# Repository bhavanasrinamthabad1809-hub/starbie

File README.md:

# RECTANGLEBIE (3 button edition)

so basically starbie is a tiny digital pet that lives on your desk, kinda like a tamagotchi lol. it walks around a little oled screen, reacts when you tilt or shake it, shows the temperature and humidity, and now it also gets happy when you press its 3rd button.

# WHY I MADE THIS
to learn hardware simple . this is my first ever pcb so yeahh so excited to get my hands on it .

# WHAT IT DOES
button 1 opens the menu. when the menu is open you tilt it to move the ball over NAP, PLAY, FEED or PET, then press button 1 again to pick one. button 2 shows or hides the stats like joy, energy, fullness, temperature and humidity. button 3 makes starbie happy, it hops and hearts float up and sparkles twinkle. if you shake it, starbie does a shake reaction. it also saves its stats so it remembers how it was doing after you unplug it.

# HOW IT WORKS
the XIAO ESP32-C3 is the brain. the 0.96 inch oled shows the pet and the menu. the MPU6050 feels the tilt and shake. the DHT11 reads temperature and humidity, with a 10k resistor on its data pin. the 3 mx switches are the buttons.

for the pins, the dht11 is on D1 (gpio 3), button 1 is on D2 (gpio 4), button 2 is on D3 (gpio 5), scl is on D4 (gpio 6), sda is on D5 (gpio 7) and button 3 is on D6 (gpio 21). the names on my schematic wires (gpio2, gpio3, gpio4) are just labels i typed, the real gpio numbers are the ones i just said.

# WHAT I CHANGED FROM THE GUIDE
i added a 3rd button because the guide only has 2, that was my twist for the project. i also made a happy animation for it, so when you press it starbie hops, hearts float up and sparkles twinkle for a few seconds, and its joy goes up. the last thing is that my scl and sda are swapped compared to the guide's table, so the numbers in the code are swapped too.

# THE PCB
made in kicad. i wanted a cloud shaped pcb with teddy ears so i used the curve lines to make the edge cut, which was harder than i thought lol. the pcb size also had to be under 100x100mm so i kept moving the parts and the edge cuts closer together to make it smaller. there is a gnd pour on both copper layers. i also added some art on the silkscreen and 3d models for the parts so the render looks nice.

a lot of stuff went wrong. some parts like the esp32 weren't in kicad search so i had to import them from the care package. my labels in the schematic weren't touching the parts so nothing was actually connected, and someone in the slack helped me figure that out. one trace was also unconnected in the drc and i had to fix it.

# FLIMWARE
it's one arduino sketch based on the guide's code, with changes in the code , adding 3 button , changing the character with image app , specifically telling the reaction to the pet to nap rest happy jump excited , i mean maybe i will change the character and code when i see how actually  see it performs i dont have any idea right now about it how it works so yeahh ,menu opening much more.

## STATUS
the schematic and pcb layout are done and the firmware done. i haven't tested it on the real board yet because it's not built.(SOON)

## Bill of Materials

| Component    | Quantity | Description         | Source                       | Price |
| ------------ | -------: | ------------------- | ---------------------------- | ----: |
| ESP32-C3     |        1 | Microcontroller     | [link](https://robu.in/product/seeed-studio-xiao-esp32c3-tiny-mcu-board-with-wi-fi-and-ble-battery-charge-supported-power-efficiency-and-rich-interface/) | 749  |
| OLED Display |        1 | Small display       | [link](https://robocraze.com/products/0-96in-oled-display-module-4pin) |169 |
| 10K Resistor |        1 | Pull-up resistor    | [link](https://robocraze.com/products/10k-resistor-pack-of-10) |13|
| switches  |        3 | User input buttons  | [link](https://amzn.in/d/0aKbDkSN) | 359 |
| DHT11  |        1 | environment sensor  | [link](https://robu.in/product/serial-dht11-temperature-and-humidity-sensor/) | 289 |
| PCB          |        1 | Custom-designed PCB | [link](https://jlcpcb.com/)  | 1330|
| MPU6050 | 1 | 6-axis motion sensor module (GY-521) | [Link](https://robocraze.com/products/mpu-6050-triple-axis-accelerometer-gyroscope-module) | 151 |

all in rupees indian currency 

# CREDITS
 made for half life by hack club. thanks to the people in the half life slack who helped ME when i got stuck.

and all the Beautifull  sticker owner pins

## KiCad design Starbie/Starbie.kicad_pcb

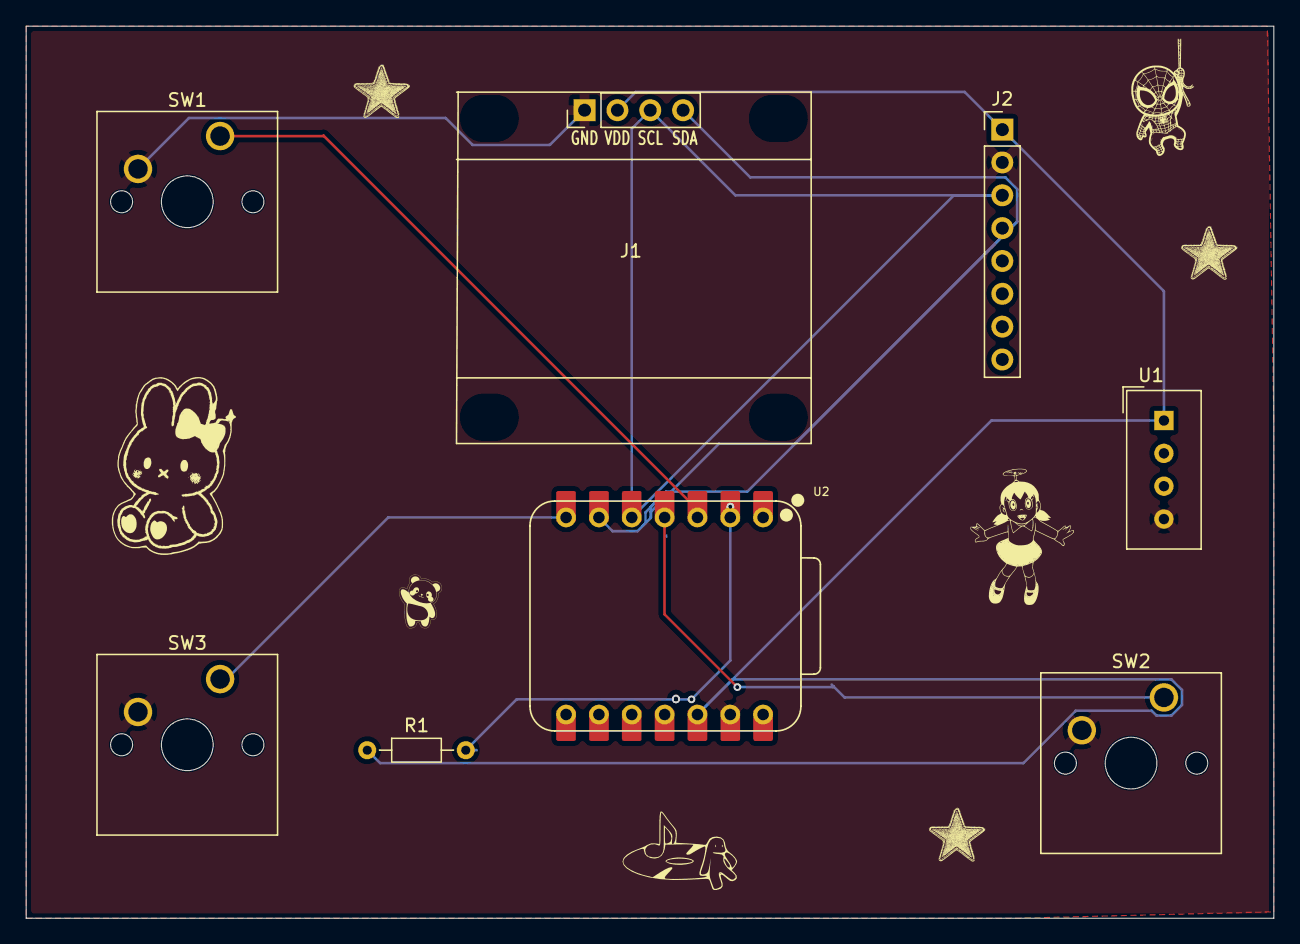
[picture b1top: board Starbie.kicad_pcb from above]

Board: 2 copper layers, 96.5 x 69.0 mm, 8 parts (0 on the bottom side), 8 nets.

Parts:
J1: Conn_01x04_Pin; Display_128x64_096_I2C
J2: Conn_01x08_Pin; PinHeader_1x08_P2.54mm_Vertical
R1: 10K; R_Axial_DIN0204_L3.6mm_D1.6mm_P7.62mm_Horizontal
SW1, SW2, SW3: SW_Push; SW_Cherry_MX_1.00u_PCB
U1: DHT11; Aosong_DHT11_5.5x12.0_P2.54mm
U2: XIAO-ESP32-C3-SMD; XIAO-ESP32-C6-DIP

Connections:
+3.3V: J1.2, J2.1, R1.1, U1.1 (VDD), U2.12 (3V3_OUT)
/dht11 data: R1.2, U2.2 (D1)
/gpio2: SW1.1, U2.3 (D2)
/gpio3: SW2.1, U2.4 (D3)
/gpio4: SW3.1, U2.7 (D6)
/scl: J1.3, J2.3, U2.5 (D4)
/sda: J1.4, J2.4, U2.6 (D5)
GND: J1.1, J2.2, SW1.2, SW2.2, SW3.2, U1.4 (GND), U2.13 (GND)
